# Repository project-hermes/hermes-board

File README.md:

# hermes-board
Circuit board for hermes sensor

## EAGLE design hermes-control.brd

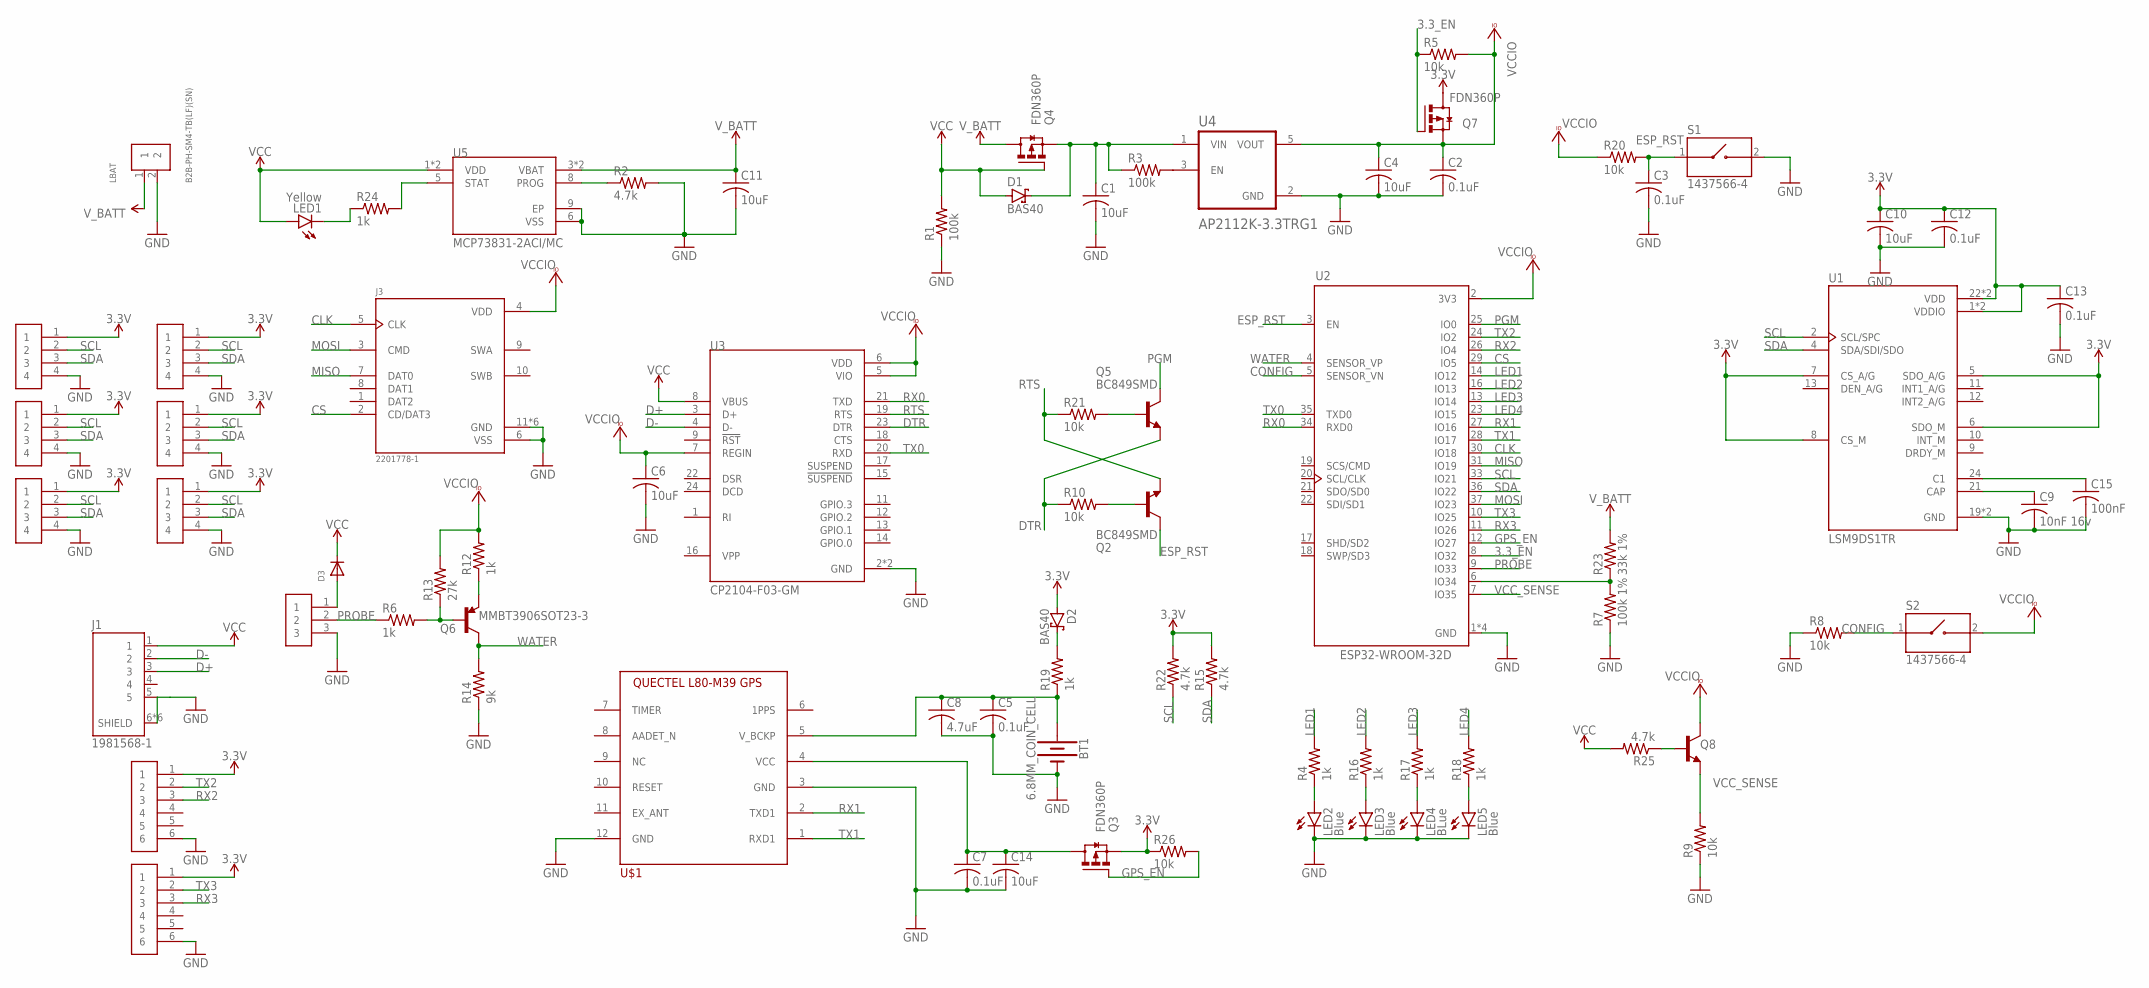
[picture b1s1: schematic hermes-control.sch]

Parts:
BT1: 6.8MM_COIN_CELL; BATTCON-6.8MM
C1, C4, C6, C10, C11, C14: 10uF; C0603
C2, C3, C5, C7, C12, C13: 0.1uF; C0603
C8: 4.7uF; C0603
C9: 10nF 16v; C0603
C15: 100nF; C0603
D1, D2: BAS40; SOT23
D3: DIODE_SOD-123FL; SOD-123FL
J1: 1981568-1; TE_1981568-1
J3: 2201778-1; TE_2201778-1
LBAT: B2B-PH-SM4-TB(LF)(SN); JST_B2B-PH-SM4-TB(LF)(SN)
LED1: Yellow; CHIPLED_0805
LED2, LED3, LED5: Blue; CHIPLED_0805
LED4: BLue; CHIPLED_0805
Q2, Q5: BC849SMD; SOT23-BEC
Q3, Q4, Q7: FDN360P; SUPER-SOT3
Q6: MMBT3906SOT23-3; SOT23-3
Q8: MMBT2222A; SOT23
R1, R3: 100k; R0603
R2, R15, R22, R25: 4.7k; R0603
R4, R6, R12, R16, R17, R18, R19, R24: 1k; R0603
R5, R8, R9, R10, R20, R21, R26: 10k; R0603
R7: 100k 1%; R0603
R13: 27k; R0603
R14: 9k; R0603
R23: 33k 1%; R0603
S1, S2: 1437566-4; SW_1437566-4
U1: LSM9DS1TR; PQFN43P300X350X102-24N
U2: ESP32-WROOM-32D; MODULE_ESP32-WROOM-32D
U3: CP2104-F03-GM; QFN50P400X400X80-25N
U4: AP2112K-3.3TRG1; SOT95P285X140-5N
U5: MCP73831-2ACI/MC; SON50P200X300X100-9N
U$1: L80_GNSS_MODULE; L80_PACKAGE
U$2: JST-GH-3VERT; JST-GH-TOP-3
U$3, U$4, U$5, U$9, U$10, U$11: JST-GH-4TOP; JST-GH-TOP-4
U$7, U$8: JST-GH-6TOP-ENTRY; JST-GH-TOP-6

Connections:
3.3V: C10.1, C12.1, C13.1, D2.1 (A), Q3.2 (S), Q7.3 (D), R15.2, R22.2, R26.1, U1.1 (VDDIO), U1.3 (VDDIO), U1.5 (SDO_A/G), U1.6 (SDO_M), U1.7 (CS_A/G), U1.8 (CS_M), U1.22 (VDD), U1.23 (VDD), U$3.1, U$4.1, U$5.1, U$7.1, U$8.1, U$9.1, U$10.1, U$11.1
3.3_EN: Q7.1 (G), R5.1, U2.8 (IO32)
CLK: J3.5 (CLK), U2.30 (IO18)
CONFIG: R8.2, S2.1, U2.5 (SENSOR_VN)
CS: J3.2 (CD/DAT3), U2.29 (IO5)
D+: J1.3, U3.3 (D+)
D-: J1.2, U3.4 (D-)
DTR: Q5.E, R10.1, U3.23 (DTR)
ESP_RST: C3.1, Q2.C, R20.2, S1.1, U2.3 (EN)
GND: BT1.-, C1.2, C2.2, C3.2, C4.2, C5.2, C6.2, C7.2, C8.2, C9.2, C10.2, C11.2, C12.2, C13.2, C14.2, C15.2, J1.5, J1.6 (SHIELD), J1.7 (SHIELD), J1.8 (SHIELD), J1.9 (SHIELD), J1.10 (SHIELD), J1.11 (SHIELD), J3.6 (VSS), J3.11 (GND), J3.12 (GND), J3.13 (GND), J3.14 (GND), J3.15 (GND), J3.16 (GND), LBAT.2, LED2.C, LED3.C, LED4.C, LED5.C, R1.1, R2.2, R7.1, R8.1, R9.1, R14.1, S1.2, U1.19 (GND), U1.20 (GND), U2.1 (GND), U2.15 (GND), U2.38 (GND), U2.39 (GND), U3.2 (GND), U3.25 (GND), U4.2 (GND), U5.6 (VSS), U5.9 (EP), U$1.3 (GND), U$1.12 (GND), U$2.3, U$3.4, U$4.4, U$5.4, U$7.6, U$8.6, U$9.4, U$10.4, U$11.4
GPS_EN: Q3.1 (G), R26.2, U2.12 (IO27)
IO13: R7.2, R23.1, U2.6 (IO34)
LED1: R4.2, U2.14 (IO12)
LED2: R16.2, U2.16 (IO13)
LED3: R17.2, U2.13 (IO14)
LED4: R18.2, U2.23 (IO15)
MISO: J3.7 (DAT0), U2.31 (IO19)
MOSI: J3.3 (CMD), U2.37 (IO23)
unnamed: R2.1, U5.8 (PROG)
unnamed: R24.2, U5.5 (STAT)
unnamed: LED1.C, R24.1
unnamed: C1.1, D1.3 (C), Q4.2 (S), R3.1, U4.1 (VIN)
unnamed: R3.2, U4.3 (EN)
unnamed: C7.1, C14.1, Q3.3 (D), U$1.4 (VCC)
unnamed: D3.A, U$2.1
unnamed: C9.1, U1.21 (CAP)
unnamed: C15.1, U1.24 (C1)
unnamed: Q6.1 (B), R6.2, R13.1
unnamed: Q6.2 (E), R12.1
unnamed: BT1.+, C5.1, C8.1, R19.1, U$1.5 (V_BCKP)
unnamed: D2.3 (C), R19.2
unnamed: LED2.A, R4.1
unnamed: LED3.A, R16.1
unnamed: Q2.B, R10.2
unnamed: Q5.B, R21.2
unnamed: LED4.A, R17.1
unnamed: LED5.A, R18.1
unnamed: Q8.1 (B), R25.1
PGM: Q5.C, U2.25 (IO0)
PROBE: R6.1, U2.9 (IO33), U$2.2
RTS: Q2.E, R21.1, U3.19 (RTS)
RX0: U2.34 (RXD0), U3.21 (TXD)
RX1: U2.27 (IO16), U$1.2 (TXD1)
RX2: U2.26 (IO4), U$7.3
RX3: U2.11 (IO26), U$8.3
SCL: R22.1, U1.2 (SCL/SPC), U2.33 (IO21), U$3.2, U$4.2, U$5.2, U$9.2, U$10.2, U$11.2
SDA: R15.1, U1.4 (SDA/SDI/SDO), U2.36 (IO22), U$3.3, U$4.3, U$5.3, U$9.3, U$10.3, U$11.3
TX0: U2.35 (TXD0), U3.20 (RXD)
TX1: U2.28 (IO17), U$1.1 (RXD1)
TX2: U2.24 (IO2), U$7.2
TX3: U2.10 (IO25), U$8.2
VCC: D1.1 (A), D3.C, J1.1, LED1.A, Q4.1 (G), R1.2, R25.2, U3.8 (VBUS), U5.1 (VDD), U5.2 (VDD)
VCCIO: C2.1, C4.1, C6.1, J3.4 (VDD), Q7.2 (S), Q8.3 (C), R5.2, R12.2, R13.2, R20.1, S2.2, U2.2 (3V3), U3.5 (VIO), U3.6 (VDD), U3.7 (REGIN), U4.5 (VOUT)
VCC_SENSE: Q8.2 (E), R9.2, U2.7 (IO35)
V_BATT: C11.1, LBAT.1, Q4.3 (D), R23.2, U5.3 (VBAT), U5.4 (VBAT)
WATER: Q6.3 (C), R14.2, U2.4 (SENSOR_VP)

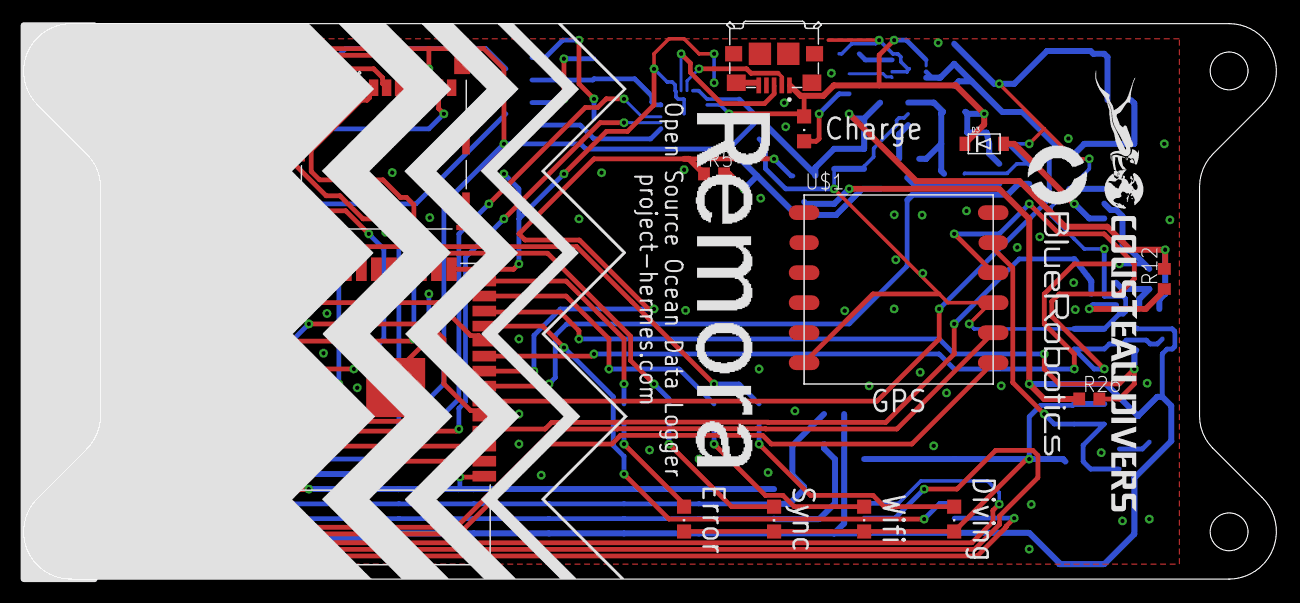
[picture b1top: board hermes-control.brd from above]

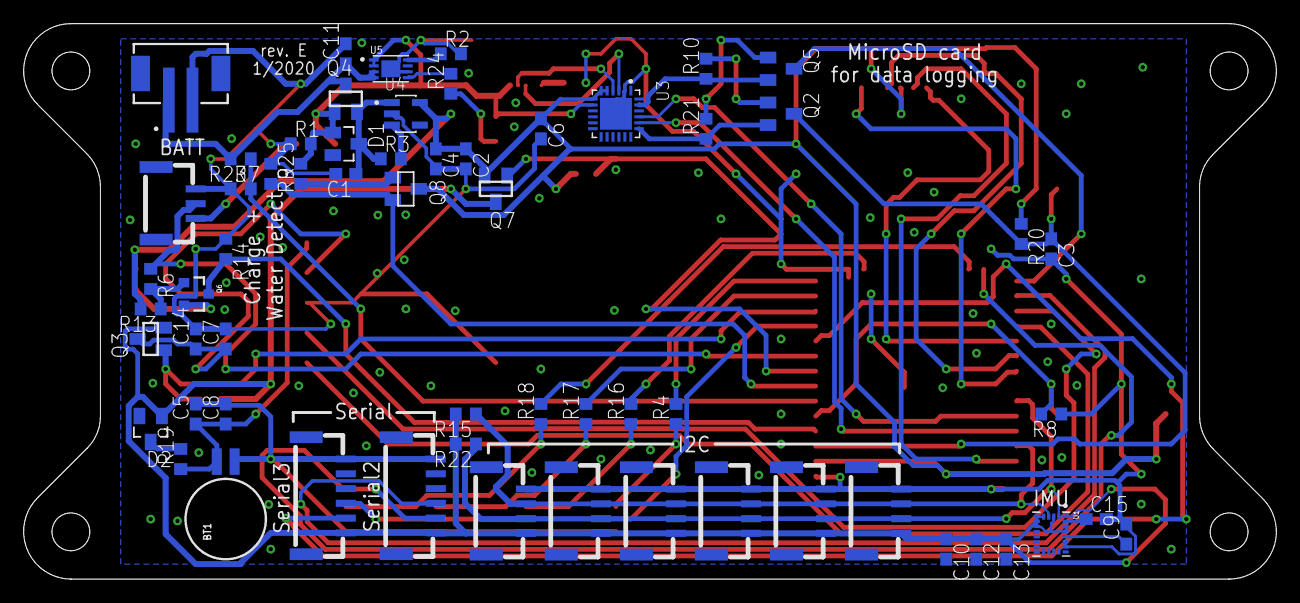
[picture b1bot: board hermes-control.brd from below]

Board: 2 copper layers, 106.0 x 47.0 mm, 80 parts (61 on the bottom side), 56 nets.

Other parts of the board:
U$6: REMORA-SILKSCREEN-CHEVRON
U$12: BR-FULL-LOGO-MEDIUM
U$13: COUSTEAU-DIVERS-LOGO-MEDIUM
U$15: REMORA-TEXT-INTER

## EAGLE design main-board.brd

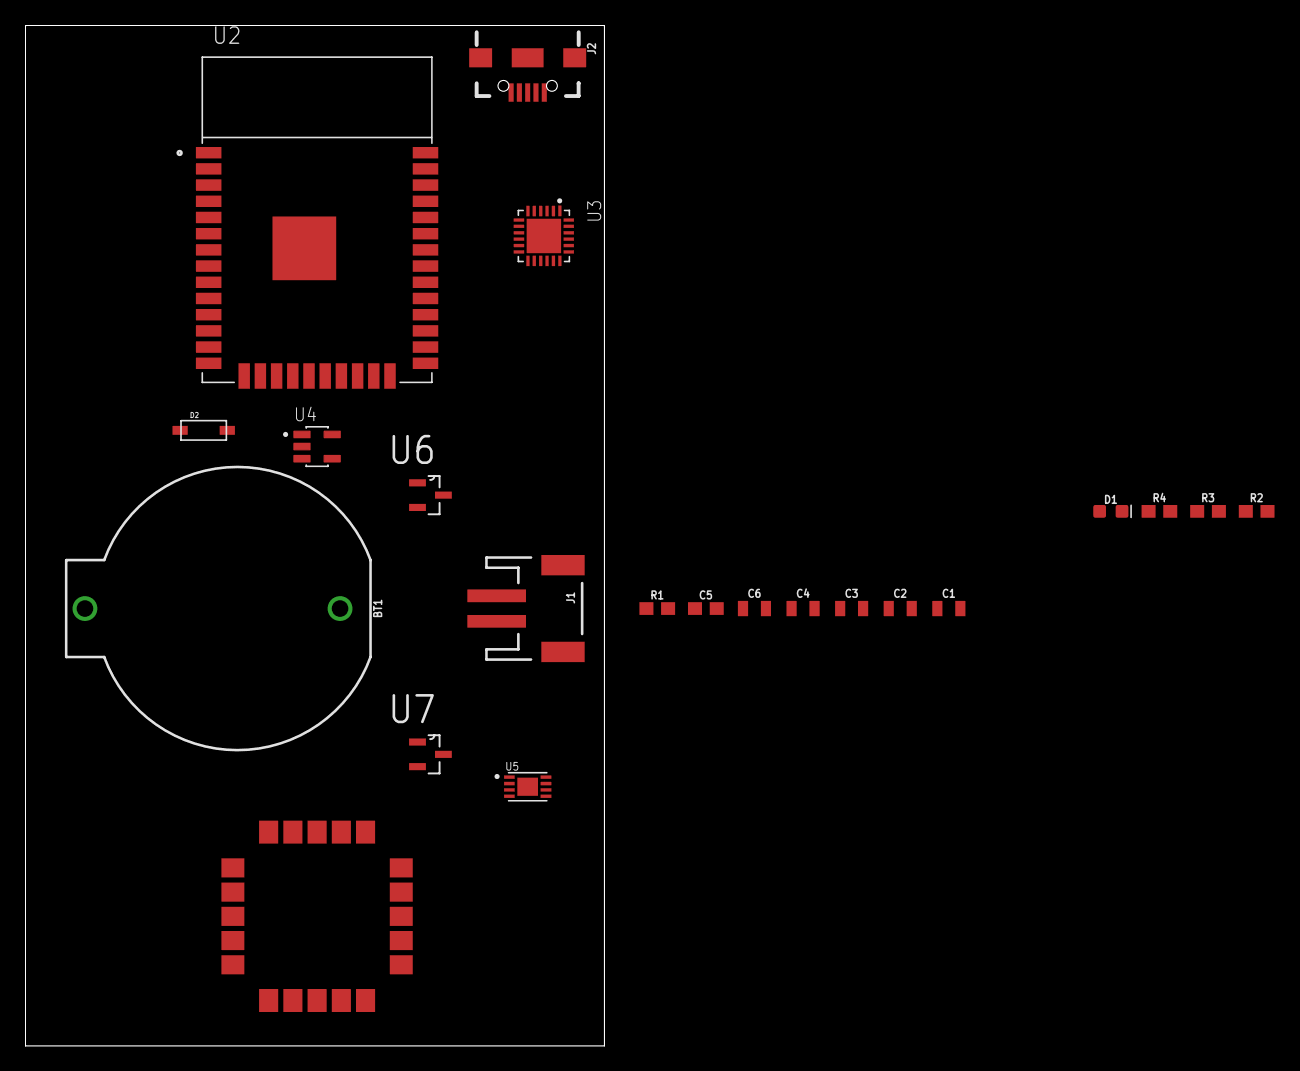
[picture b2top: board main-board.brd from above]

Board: 2 copper layers, 45.4 x 80.0 mm, 22 parts (0 on the bottom side), 19 nets, no tracks yet.

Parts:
BT1: BATTCOM_20MM_PTH
C1, C2, C4, C6: 10uF; 0805
C3: 1.0uF; 0805
C5: 0.1uF; 0603
D1: Yellow; LED-0603
D2: SOD-123
IC1: SAM-M8Q
J1: JST-2-SMD
J2: USB-B-MICRO-SMD
R1: 4.7k; 0603
R2: 1k; 0603
R3, R4: 100k; 0603
U2: ESP32-WROOM-32D; MODULE_ESP32-WROOM-32D
U3: CP2104-F03-GM; QFN50P400X400X80-25N
U4: AP2112K-3.3TRG1; SOT95P285X140-5N
U5: MCP73831-2ACI/MC; SON50P200X300X100-9N
U6, U7: DMG3415U-7; SOT95P240X105-3N

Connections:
3.3V: C2.1, C3.1, U2.2, U4.5, U7.2
GND: BT1.2, C1.2, C2.2, C3.2, C4.2, C5.2, C6.2, IC1.1, IC1.4, IC1.5, IC1.6, IC1.10, IC1.11, IC1.15, IC1.16, IC1.20, J1.1, J2.GND, R1.2, R3.1, U2.1, U2.15, U2.38, U2.39, U3.2, U3.25, U4.2, U5.6
GPSENABLE: U2.28, U7.1
GPSRX: IC1.13, U2.31
GPSTX: IC1.14, U2.30
unnamed: R1.1, U5.8
unnamed: R2.2, U5.5
unnamed: D1.C, R2.1
unnamed: C4.1, D2.C, R4.1, U4.1, U6.3
unnamed: R4.2, U4.3
unnamed: C5.1, IC1.2, IC1.17, U7.3
unnamed: BT1.1, IC1.3
unnamed: J2.D+, U3.3
unnamed: J2.D-, U3.4
REGIN: C6.1, U3.5, U3.6, U3.7
USBRX: U2.34, U3.21
USBTX: U2.35, U3.20
VCC: D1.A, D2.A, J2.VBUS, R3.2, U3.8, U5.1, U5.2, U6.1
V_BATT: C1.1, J1.2, U5.3, U5.4, U6.2

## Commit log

2019-01-24 init
2019-01-24 create power managment
2019-01-24 added board
2019-01-24 added board design
2019-01-27 Update issue templates
2019-01-27 rename
2019-01-27 added new board
2019-01-28 new gps and new layout
2019-02-26 added sd, leds, buttons, and clean up
2019-02-27 added i2c connetions and buss
2019-02-28 added uart serial ports
2019-02-28 added 9DOF IMU
2019-03-07 added the board layout
2019-03-19 updated componets to match bom
2019-03-19 add library
2019-04-02 started to wries a few things
2019-04-04 stuck trying to finish wiring
2019-04-08 everything is connected but ground
2019-04-08 it is done
2019-04-16 lets clean this up
2019-04-16 replaced all componets with generics
2019-04-17 addresed issue comments
2019-04-18 updated resistors and addressed comments
2019-04-23 updated GPIO
2019-04-25 addressed more reviews
2019-05-01 added two more i2c connections
2019-05-04 Update board outline.
2019-05-04 new layout with main componets
2019-05-05 all componets placed
2019-05-05 routed single sides with no vias
2019-05-05 ripped up all signal
2019-05-05 almost everything is connected
2019-05-06 all connections made
2019-05-06 added gnd plane
2019-05-06 fixed air wires and isolated 0.1
2019-05-06 adjusted vias and ground planes
2019-05-07 added test and cleaned up ground plane
2019-05-09 more changes and dimension is stuck
2019-05-10 removed deminsion
2019-05-10 more gnd
2019-05-31 flip sd card and connect vcc to usb uart chip
2019-06-01 new bat connector
2019-06-26 flipped fet
2019-06-26 changed from 3.3 to vccio
2019-06-28 changed batt connection
2019-08-05 more vccio
2019-08-07 Answers to Questions: - ESP32_RST looks like it should be a 0.1uF not 1uF (p15) -- fixed - similarly, the reference decoupling caps for 3V3 (pin 2) are 10uF and 0.1uF but you have 10uF and 1uF (on VC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
2019-08-10 updated resisotrs
2019-12-05 Update silkscreen design and add logos to library.
2020-01-26 Change silkscreen back to Remora and clean up lots of small things.
2020-01-27 Move one label that was under SMT components.

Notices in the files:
parts and their libraries:
SparkFun-Batteries: Licensing: Creative Commons ShareAlike 4.0 International - https://creativecommons.org/licenses/by-sa/4.0
